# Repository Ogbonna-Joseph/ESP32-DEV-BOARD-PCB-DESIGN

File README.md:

# ESP32-DEV-BOARD-PCB-DESIGN
Design of an ESP32 Development Board
# SCHEMATICS DESIGN

# PCB ROUTE

# 3D PCB DESIGN

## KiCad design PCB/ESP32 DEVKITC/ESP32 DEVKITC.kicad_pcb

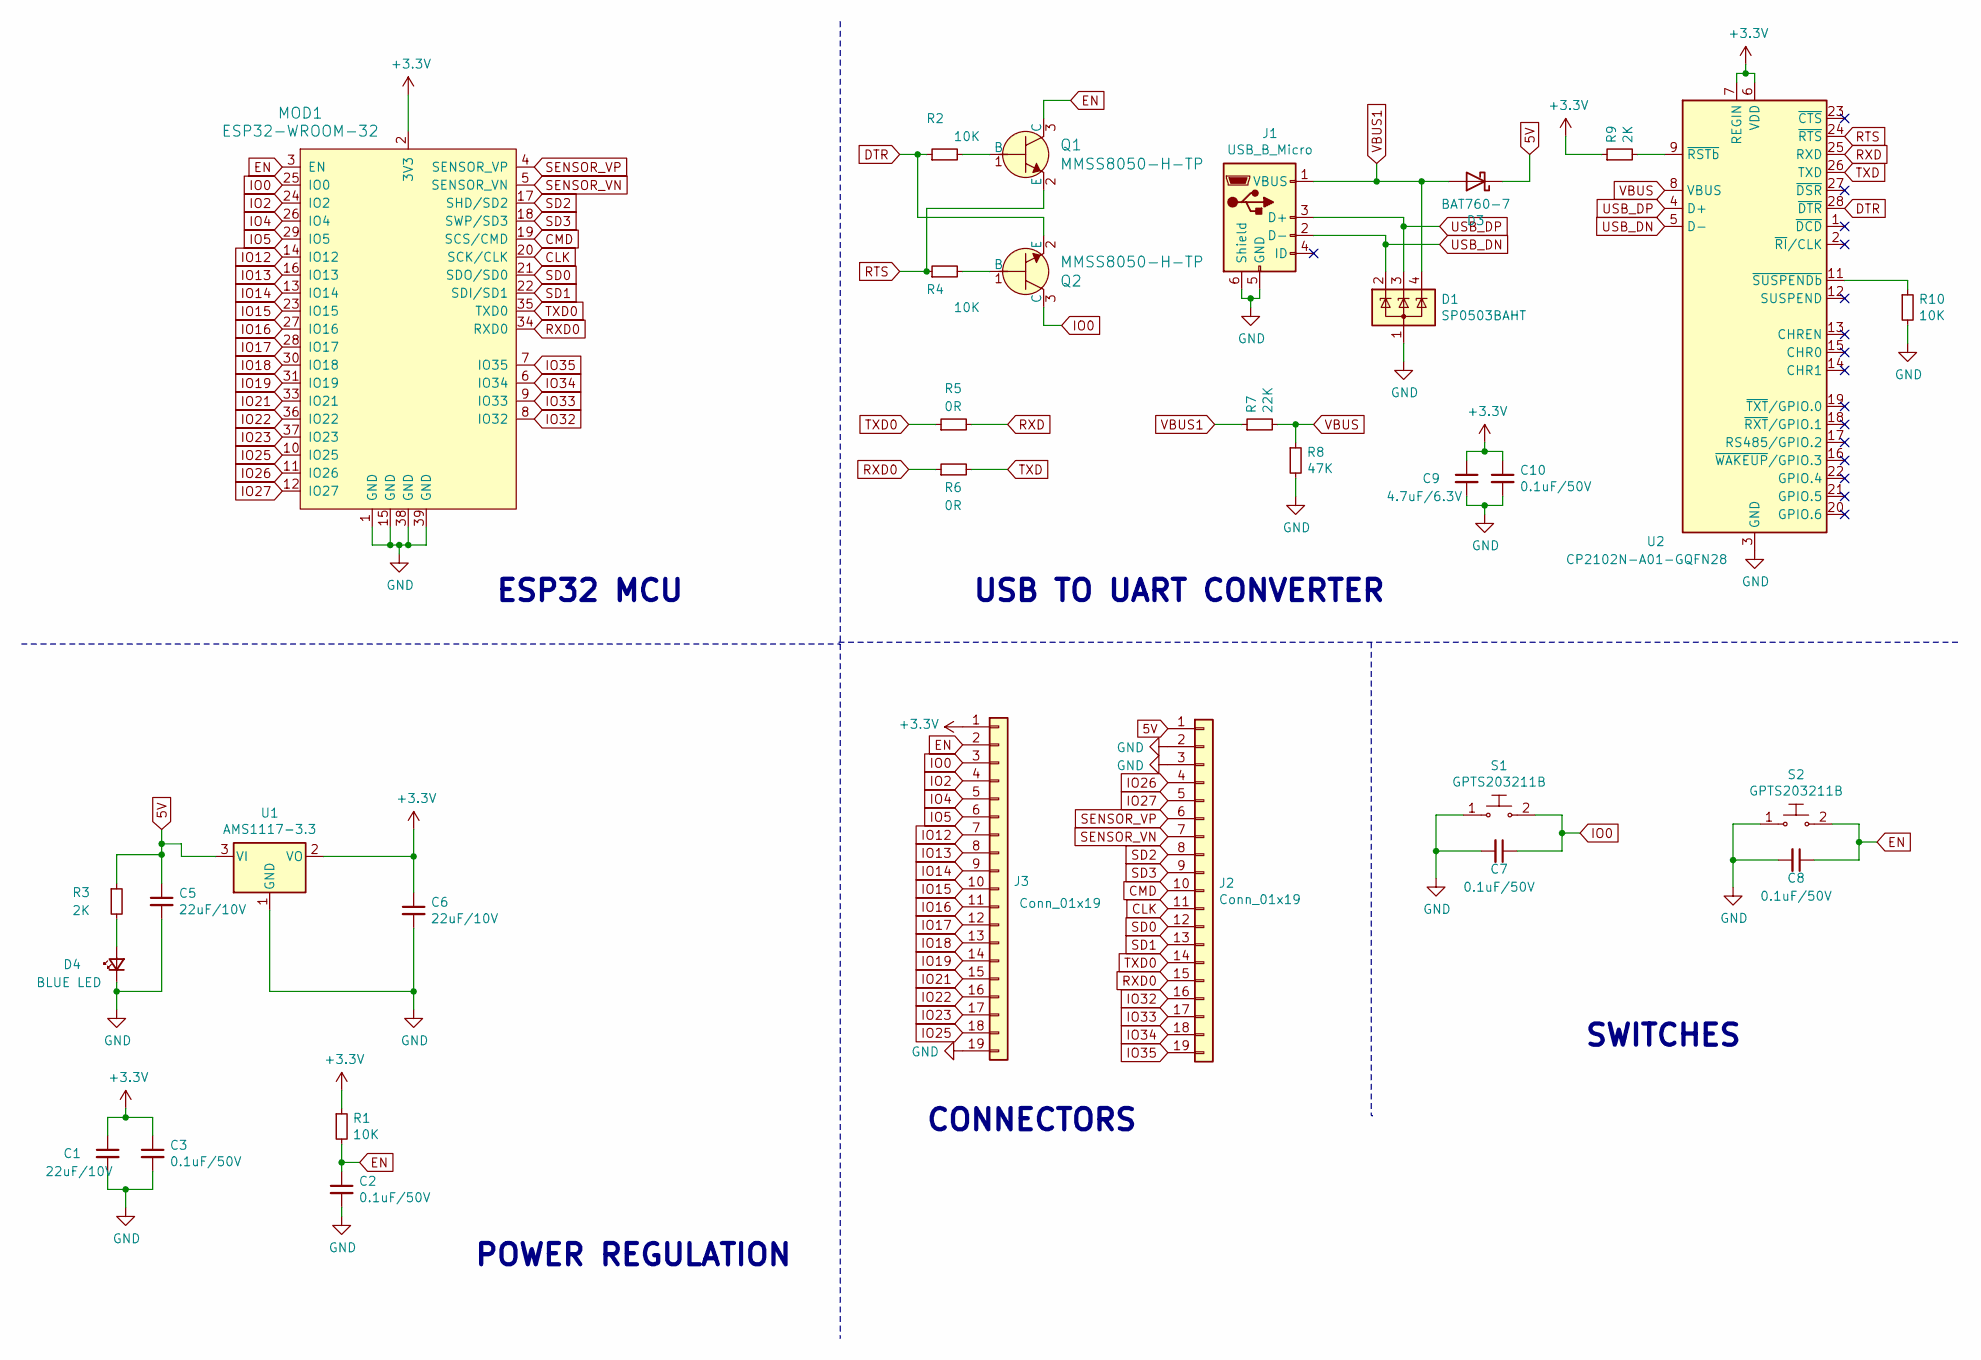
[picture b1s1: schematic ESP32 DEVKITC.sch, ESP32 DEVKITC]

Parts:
C1, C5, C6: 22uF/10V; C_0402_1005Metric_Pad0.74x0.62mm_HandSolder
C2, C3, C7, C8, C10: 0.1uF/50V; C_0402_1005Metric_Pad0.74x0.62mm_HandSolder
C9: 4.7uF/6.3V; C_0402_1005Metric_Pad0.74x0.62mm_HandSolder
D1: SP0503BAHT; SOT-143
D3: BAT760-7; D_SOD-323
D4: BLUE LED; LED_0402_1005Metric_Pad0.77x0.64mm_HandSolder
J1: USB_B_Micro; USB_Micro-B_GCT_USB3076-30-A
J2, J3: Conn_01x19; PinHeader_1x19_P2.54mm_Vertical
MOD1: ESP32-WROOM-32; ESP32-WROOM-32D; MPN ESP32-WROOM-32; Digi-Key_PN 1904-1010-1-ND
Q1, Q2: MMSS8050-H-TP; SOT-23-3; MPN MMSS8050-H-TP; Digi-Key_PN MMSS8050-H-TPMSCT-ND
R1, R2, R4, R10: 10K; R_0402_1005Metric_Pad0.72x0.64mm_HandSolder
R3, R9: 2K; R_0402_1005Metric_Pad0.72x0.64mm_HandSolder
R5, R6: 0R; R_0402_1005Metric_Pad0.72x0.64mm_HandSolder
R7: 22K; R_0402_1005Metric_Pad0.72x0.64mm_HandSolder
R8: 47K; R_0402_1005Metric_Pad0.72x0.64mm_HandSolder
S1, S2: GPTS203211B; SW_Push_1P1T_NO_CK_KMR2; MPN GPTS203211B; Digi-Key_PN CW181-ND
U1: AMS1117-3.3; SOT-223-3_TabPin2
U2: CP2102N-A01-GQFN28; QFN-28-1EP_5x5mm_P0.5mm_EP3.35x3.35mm

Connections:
5V: C5.1, D3.1 (K), J2.1, R3.1, U1.3 (VI)
+3V3: C1.1, C3.1, C6.1, C9.1, C10.1, J3.1, MOD1.2 (3V3), R1.1, R9.1, U1.2 (VO), U2.6 (VDD), U2.7 (REGIN)
CLK: J2.11, MOD1.20 (SCK/CLK)
CMD: J2.10, MOD1.19 (SCS/CMD)
DTR: Q2.2 (E), R2.1, U2.28 (~DTR)
EN: C2.1, C8.1, J3.2, MOD1.3 (EN), Q1.3 (C), R1.2, S2.2
GND: C1.2, C2.2, C3.2, C5.2, C6.2, C7.2, C8.2, C9.2, C10.2, D1.1 (A), D4.1 (K), J1.5 (GND), J1.6 (Shield), J2.2, J2.3, J3.19, MOD1.1 (GND), MOD1.15 (GND), MOD1.38 (GND), MOD1.39 (GND), R8.2, R10.2, S1.1, S2.1, U1.1 (GND), U2.3 (GND), U2.29 (GND)
IO0: C7.1, J3.3, MOD1.25 (IO0), Q2.3 (C), S1.2
IO2: J3.4, MOD1.24 (IO2)
IO4: J3.5, MOD1.26 (IO4)
IO5: J3.6, MOD1.29 (IO5)
IO12: J3.7, MOD1.14 (IO12)
IO13: J3.8, MOD1.16 (IO13)
IO14: J3.9, MOD1.13 (IO14)
IO15: J3.10, MOD1.23 (IO15)
IO16: J3.11, MOD1.27 (IO16)
IO17: J3.12, MOD1.28 (IO17)
IO18: J3.13, MOD1.30 (IO18)
IO19: J3.14, MOD1.31 (IO19)
IO21: J3.15, MOD1.33 (IO21)
IO22: J3.16, MOD1.36 (IO22)
IO23: J3.17, MOD1.37 (IO23)
IO25: J3.18, MOD1.10 (IO25)
IO26: J2.4, MOD1.11 (IO26)
IO27: J2.5, MOD1.12 (IO27)
IO32: J2.16, MOD1.8 (IO32)
IO33: J2.17, MOD1.9 (IO33)
IO34: J2.18, MOD1.6 (IO34)
IO35: J2.19, MOD1.7 (IO35)
unnamed: D4.2 (A), R3.2
unnamed: Q1.1 (B), R2.2
unnamed: Q2.1 (B), R4.2
unnamed: R9.2, U2.9 (~RSTb)
unnamed: R10.1, U2.11 (~SUSPENDb)
RTS: Q1.2 (E), R4.1, U2.24 (~RTS)
RXD: R5.2, U2.25 (RXD)
RXD0: J2.15, MOD1.34 (RXD0), R6.1
SD0: J2.12, MOD1.21 (SDO/SD0)
SD1: J2.13, MOD1.22 (SDI/SD1)
SD2: J2.8, MOD1.17 (SHD/SD2)
SD3: J2.9, MOD1.18 (SWP/SD3)
SENSOR_VN: J2.7, MOD1.5 (SENSOR_VN)
SENSOR_VP: J2.6, MOD1.4 (SENSOR_VP)
TXD: R6.2, U2.26 (TXD)
TXD0: J2.14, MOD1.35 (TXD0), R5.1
USB_DN: D1.2 (K), J1.2 (D-), U2.5 (D-)
USB_DP: D1.3 (K), J1.3 (D+), U2.4 (D+)
VBUS: R7.2, R8.1, U2.8 (VBUS)
VBUS1: D1.4 (K), D3.2 (A), J1.1 (VBUS), R7.1

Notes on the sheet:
POWER REGULATION
ESP32 MCU
CONNECTORS
SWITCHES
USB TO UART CONVERTER

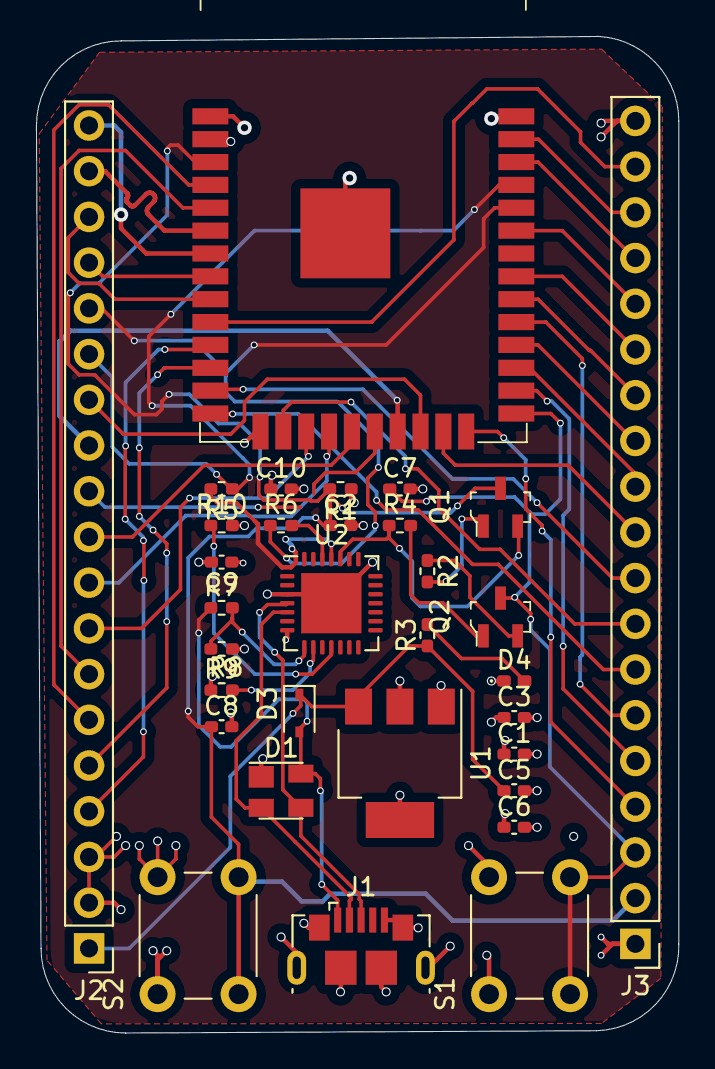
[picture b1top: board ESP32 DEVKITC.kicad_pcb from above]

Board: 4 copper layers, 35.7 x 55.4 mm, 32 parts (0 on the bottom side), 49 nets.

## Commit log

2022-01-05 Create pcb
2022-01-05 Create img
